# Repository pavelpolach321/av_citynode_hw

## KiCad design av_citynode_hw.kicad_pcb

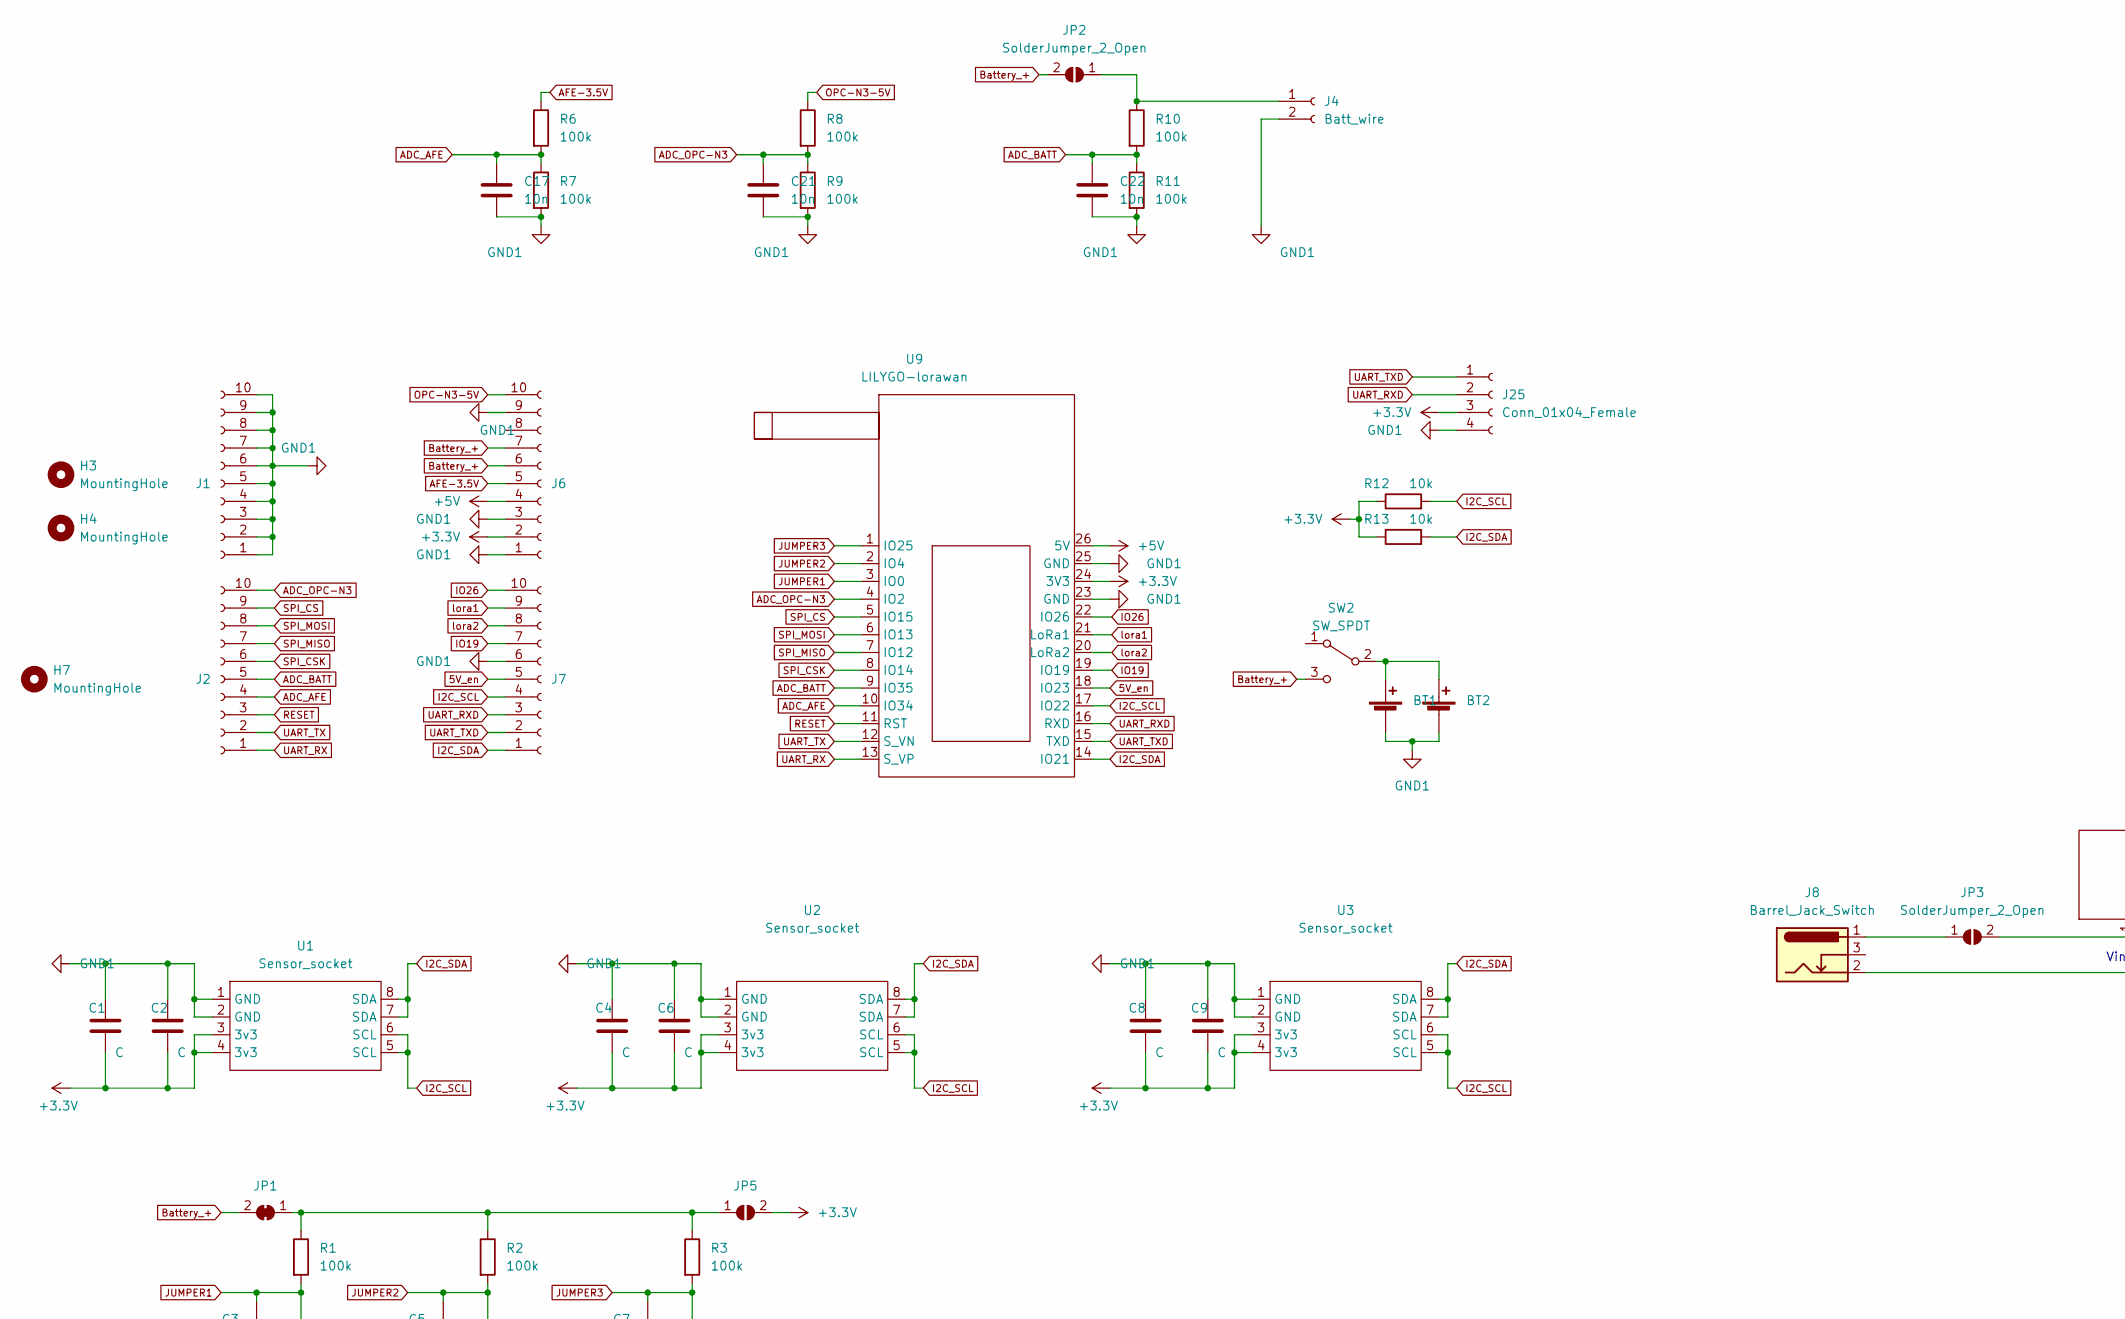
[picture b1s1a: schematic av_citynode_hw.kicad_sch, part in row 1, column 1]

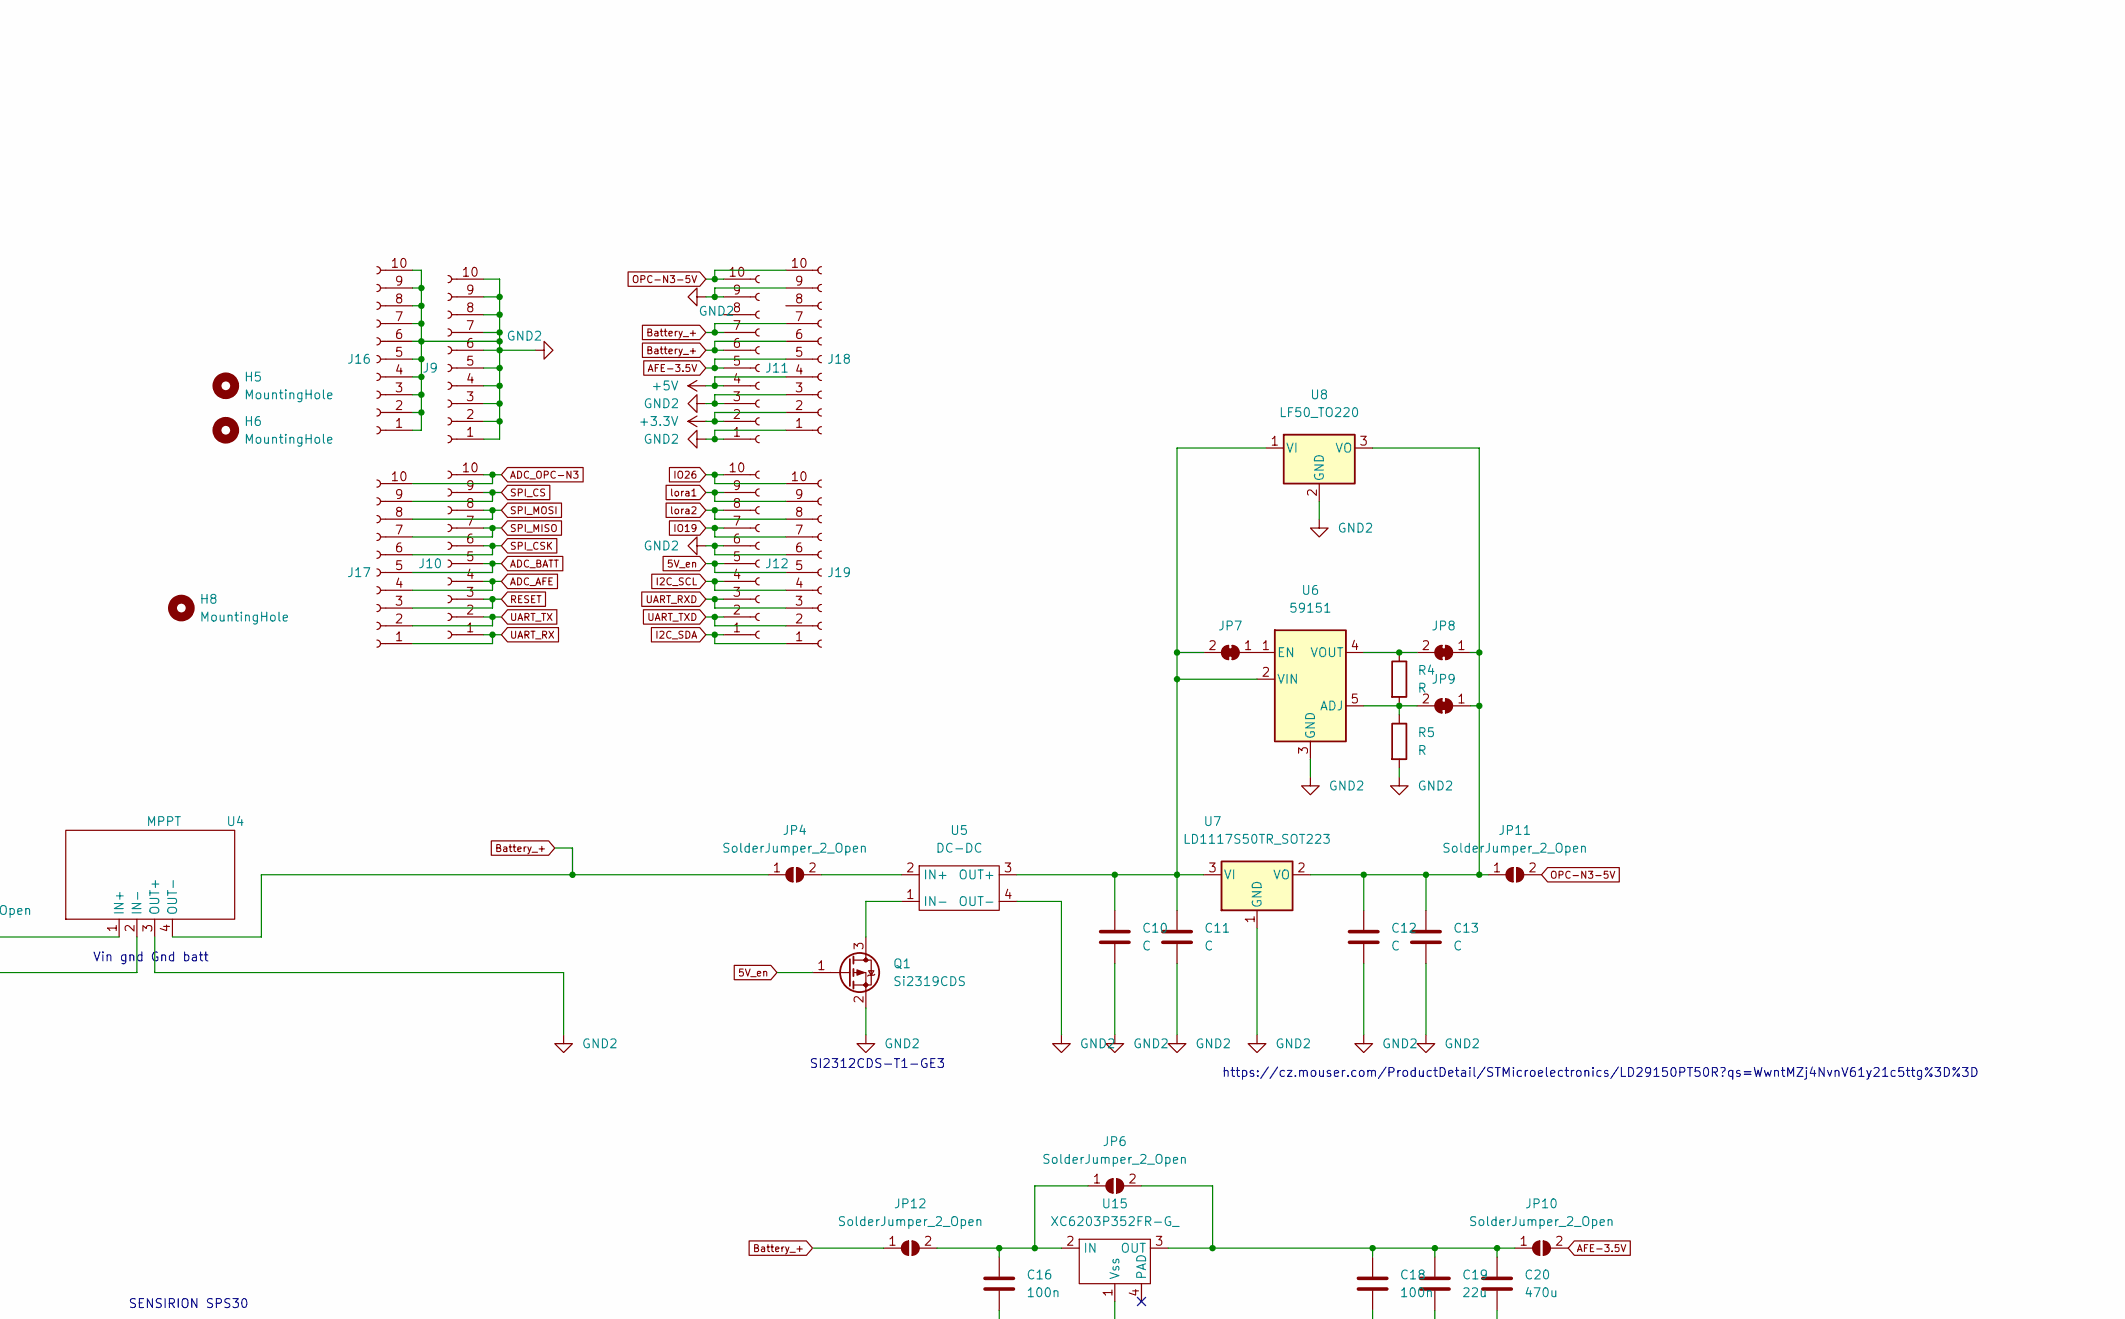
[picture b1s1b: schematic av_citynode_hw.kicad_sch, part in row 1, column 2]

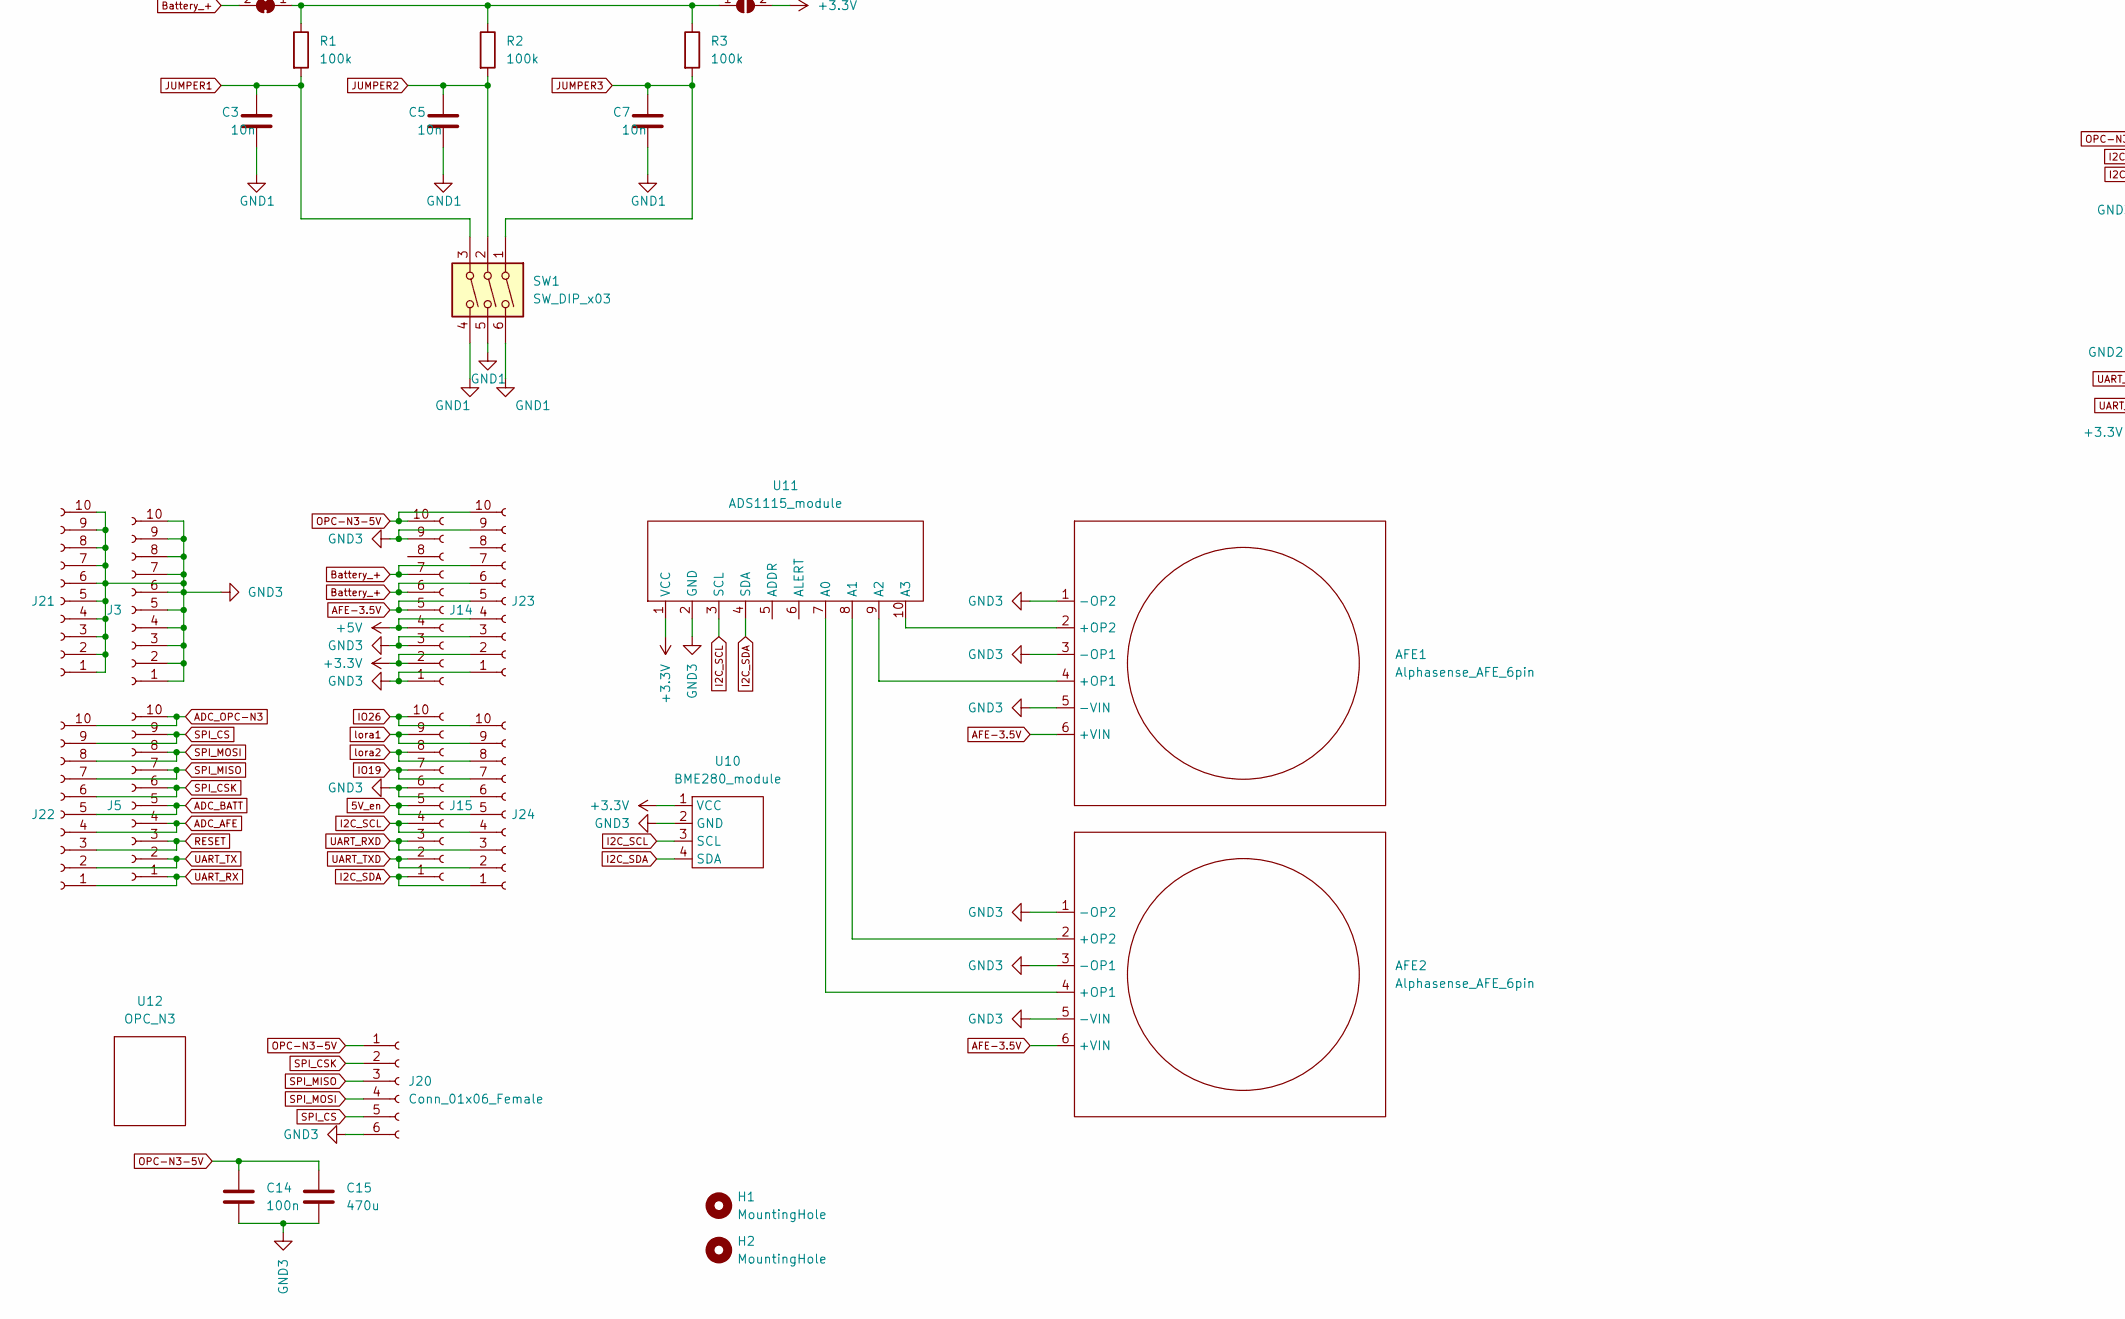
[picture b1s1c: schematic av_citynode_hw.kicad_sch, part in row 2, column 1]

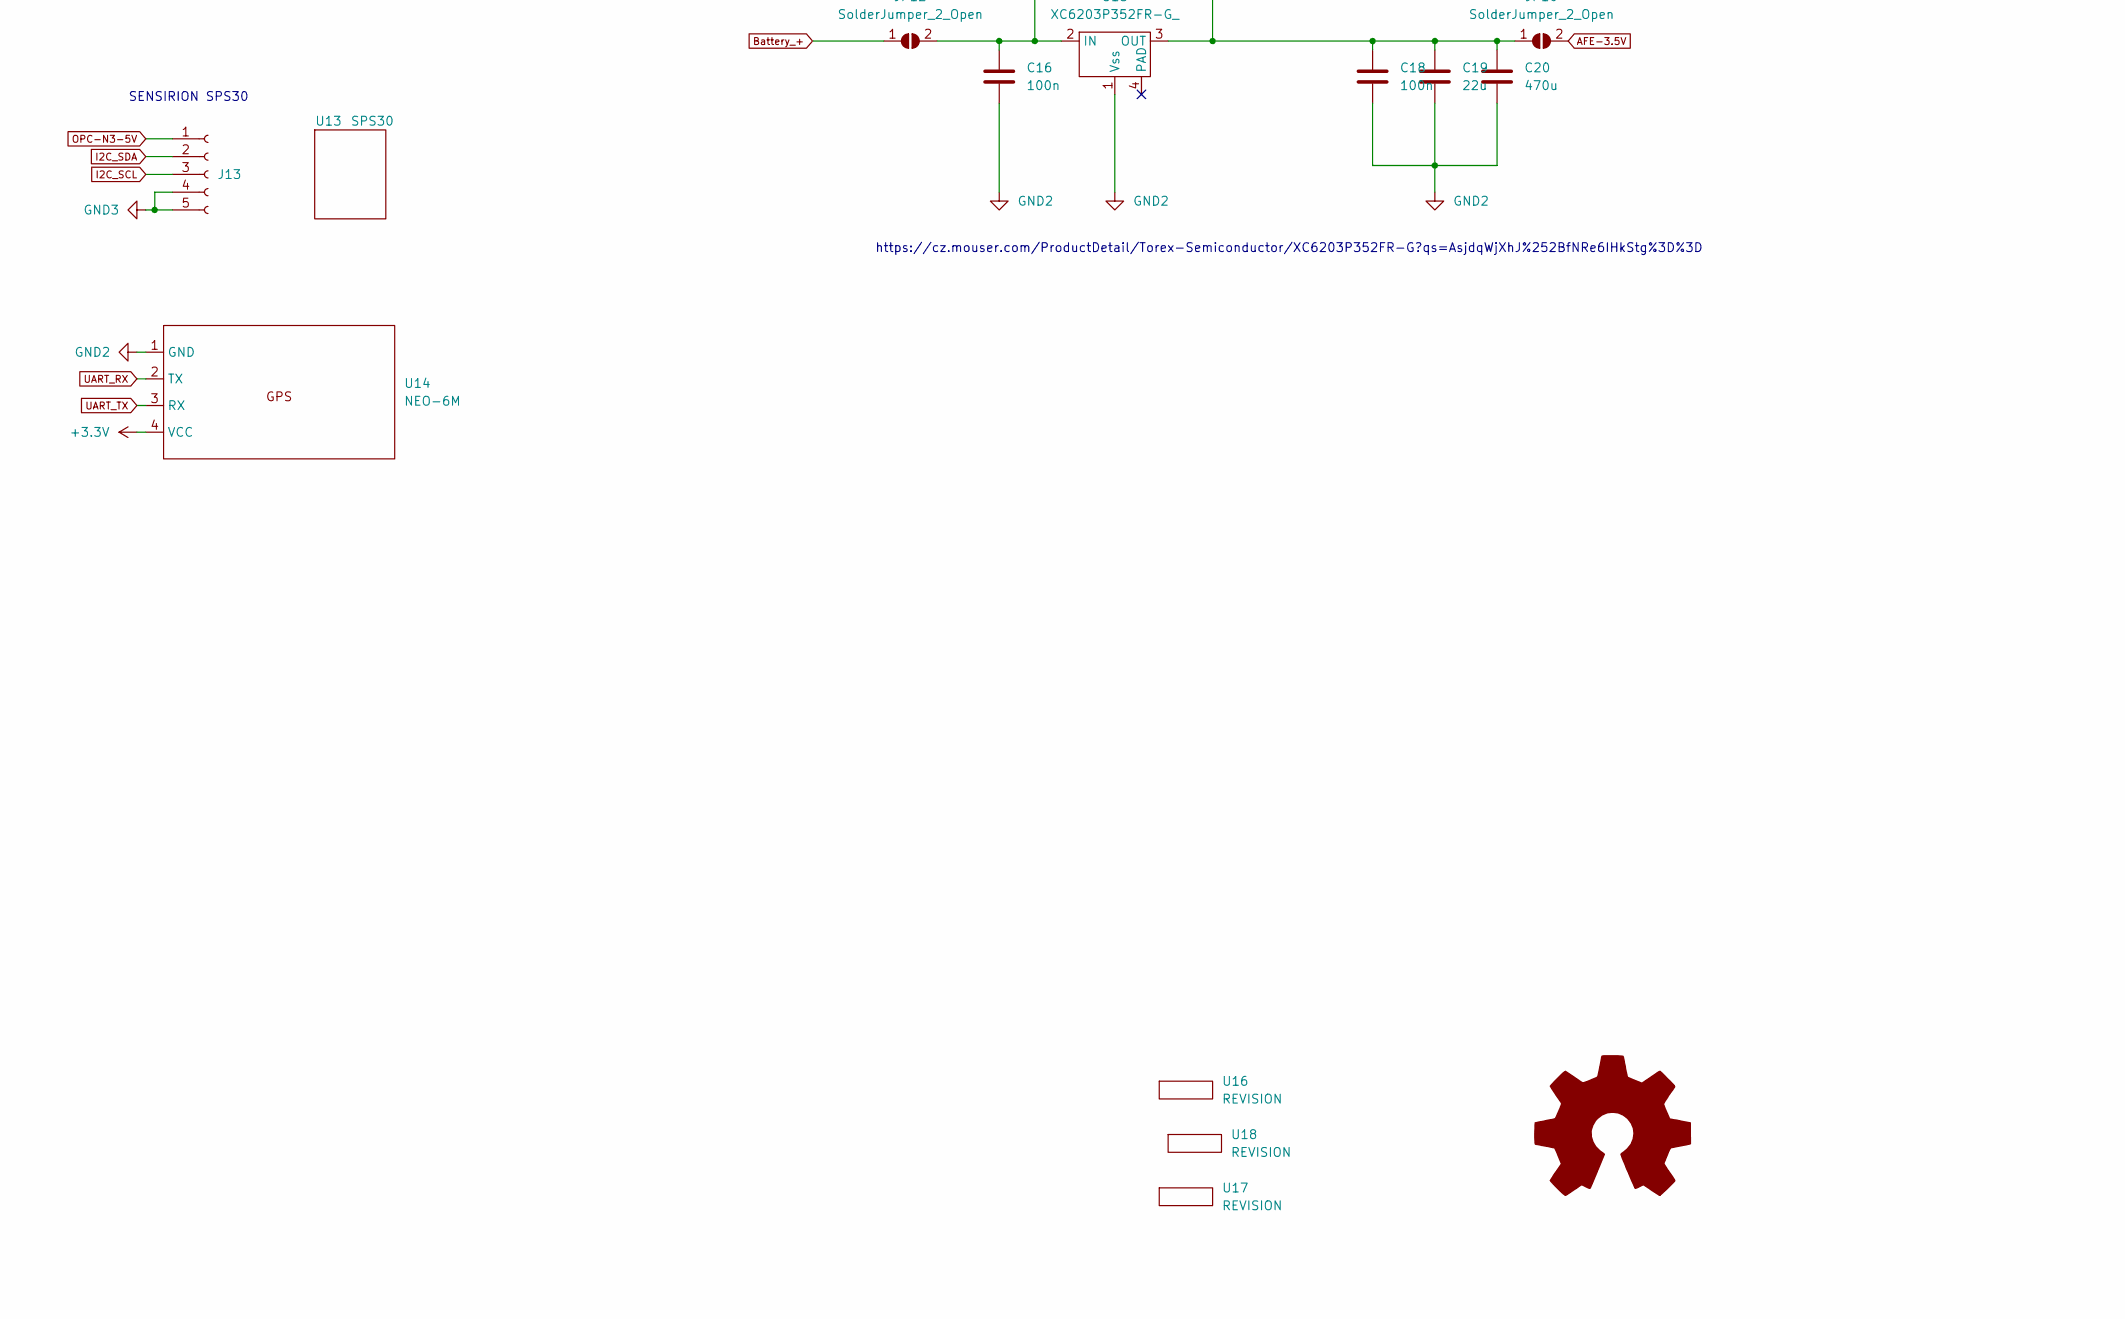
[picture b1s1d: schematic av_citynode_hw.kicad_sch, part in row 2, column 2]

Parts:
AFE1: Alphasense_AFE_6pin; Alphasense_AFE_6pin-LEFT
AFE2: Alphasense_AFE_6pin; Alphasense_AFE_6pin-RIGHT
BT1, BT2: Battery_Cell; BatteryHolder_MPD_BH-18650-PC2
C1, C2, C4, C6, C8, C9: C; C_0805_2012Metric_Pad1.18x1.45mm_HandSolder
C3, C5, C7: 10n; C_0805_2012Metric_Pad1.18x1.45mm_HandSolder
C10, C11, C12, C13: C; C_0805_2012Metric
C14, C16, C18: 100n; C_0805_2012Metric
C15: 470u; CP_Radial_D10.0mm_P3.50mm
C17, C21, C22: 10n; C_0805_2012Metric
C19: 22u; C_0805_2012Metric
C20: 470u; CP_Radial_D5.0mm_P2.50mm
H1, H2, H3, H4, H5, H6: MountingHole; MountingHole_4.3mm_M4
H7, H8: MountingHole; opc-n3-hole
J1, J2, J3, J5, J6, J7, J9, J10, J11, J12, J14, J15, J16, J17, J18, J19, J21, J22, J23, J24: Conn_01x10_Female; PinSocket_1x10_P2.54mm_Vertical
J4: Batt_wire; PinSocket_1x02_P2.54mm_Vertical
J8: Barrel_Jack_Switch; BarrelJack_Horizontal
J13: Conn_01x05_Female; PinHeader_1x05_P2.54mm_Vertical
J20: Conn_01x06_Female; PinHeader_1x06_P2.54mm_Vertical
J25: Conn_01x04_Female; PinSocket_1x04_P2.54mm_Vertical
JP1: SolderJumper_2_Bridged; SolderJumper-2_P1.3mm_Bridged_Pad1.0x1.5mm
JP2, JP3, JP4, JP6, JP10, JP11, JP12: SolderJumper_2_Open; SolderJumper-2_P1.3mm_Open_RoundedPad1.0x1.5mm
JP5: SolderJumper_2_Open; SolderJumper-2_P1.3mm_Open_Pad1.0x1.5mm
JP7, JP8, JP9: SolderJumper_2_Bridged; SolderJumper-2_P1.3mm_Open_TrianglePad1.0x1.5mm
Q1: Si2319CDS; SOT-23
R1, R2, R3: 100k; R_0805_2012Metric_Pad1.20x1.40mm_HandSolder
R4, R5: R; R_0805_2012Metric
R6, R7, R8, R9, R10, R11: 100k; R_0805_2012Metric
R12, R13: 10k; R_0805_2012Metric
SW1: SW_DIP_x03; DIP-6_W7.62mm
SW2: SW_SPDT; SW_Slide_1P2T_CK_OS102011MS2Q
U1, U2, U3: Sensor_socket; Sensor_module
U4: MPPT; DC-DC
U5: DC-DC; STEP_UP
U6: 59151; TO-263-5_TabPin3
U7: LD1117S50TR_SOT223; SOT-223-3_TabPin2
U8: LF50_TO220; TO-220-3_Vertical
U9: LILYGO-lorawan; LILYGO-LORAWAN
U10: BME280_module; BME280-module
U11: ADS1115_module; ADS1115-module
U12: OPC_N3; opc-n3
U13: SPS30
U14: NEO-6M; NEO-6M-mod
U15: XC6203P352FR-G_; SOT-223
U16, U17, U18: REVISION

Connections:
5V_en: J7.5, J12.5, J15.5, J19.5, J24.5, Q1.1 (G), U9.18 (IO23)
+3V3: C1.2, C2.2, C4.2, C6.2, C8.2, C9.2, J6.2, J11.2, J14.2, J18.2, J23.2, J25.3, JP5.2 (B), R12.1, R13.1, U1.3 (3v3), U1.4 (3v3), U2.3 (3v3), U2.4 (3v3), U3.3 (3v3), U3.4 (3v3), U9.24 (3V3), U10.1 (VCC), U11.1 (VCC), U14.4 (VCC)
+5V: J6.4, J11.4, J14.4, J18.4, J23.4, U9.26 (5V)
ADC_AFE: C17.1, J2.4, J5.4, J10.4, J17.4, J22.4, R6.2, R7.1, U9.10 (IO34)
ADC_BATT: C22.1, J2.5, J5.5, J10.5, J17.5, J22.5, R10.2, R11.1, U9.9 (IO35)
ADC_OPC-N3: C21.1, J2.10, J5.10, J10.10, J17.10, J22.10, R8.2, R9.1, U9.4 (IO2)
AFE-3.5V: AFE1.6 (+VIN), AFE2.6 (+VIN), J6.5, J11.5, J14.5, J18.5, J23.5, JP10.2 (B), R6.1
Battery_+: J6.6, J6.7, J11.6, J11.7, J14.6, J14.7, J18.6, J18.7, J23.6, J23.7, JP1.2 (B), JP2.2 (B), JP4.1 (A), JP12.1 (A), SW2.3 (C), U4.4 (OUT-)
GND1: BT1.2 (-), BT2.2 (-), C1.1, C2.1, C3.2, C4.1, C5.2, C6.1, C7.2, C8.1, C9.1, C17.2, C21.2, C22.2, J1.1, J1.2, J1.3, J1.4, J1.5, J1.6, J1.7, J1.8, J1.9, J1.10, J4.2, J6.1, J6.3, J6.9, J7.6, J25.4, R7.2, R9.2, R11.2, SW1.4, SW1.5, SW1.6, U1.1 (GND), U1.2 (GND), U2.1 (GND), U2.2 (GND), U3.1 (GND), U3.2 (GND), U9.23 (GND), U9.25 (GND)
GND2: C10.2, C11.2, C12.2, C13.2, C16.2, C18.2, C19.2, C20.2, J9.1, J9.2, J9.3, J9.4, J9.5, J9.6, J9.7, J9.8, J9.9, J9.10, J11.1, J11.3, J11.9, J12.6, J16.1, J16.2, J16.3, J16.4, J16.5, J16.6, J16.7, J16.8, J16.9, J16.10, J18.1, J18.3, J18.9, J19.6, Q1.2 (S), R5.2, U4.3 (OUT+), U5.4 (OUT-), U6.3 (GND), U7.1 (GND), U8.2 (GND), U14.1 (GND), U15.1 (Vss)
GND3: AFE1.1 (-OP2), AFE1.3 (-OP1), AFE1.5 (-VIN), AFE2.1 (-OP2), AFE2.3 (-OP1), AFE2.5 (-VIN), C14.2, C15.2, J3.1, J3.2, J3.3, J3.4, J3.5, J3.6, J3.7, J3.8, J3.9, J3.10, J13.4, J13.5, J14.1, J14.3, J14.9, J15.6, J20.6, J21.1, J21.2, J21.3, J21.4, J21.5, J21.6, J21.7, J21.8, J21.9, J21.10, J23.1, J23.3, J23.9, J24.6, U10.2 (GND), U11.2 (GND)
I2C_SCL: J7.4, J12.4, J13.3, J15.4, J19.4, J24.4, R12.2, U1.5 (SCL), U1.6 (SCL), U2.5 (SCL), U2.6 (SCL), U3.5 (SCL), U3.6 (SCL), U9.17 (IO22), U10.3 (SCL), U11.3 (SCL)
I2C_SDA: J7.1, J12.1, J13.2, J15.1, J19.1, J24.1, R13.2, U1.7 (SDA), U1.8 (SDA), U2.7 (SDA), U2.8 (SDA), U3.7 (SDA), U3.8 (SDA), U9.14 (IO21), U10.4 (SDA), U11.4 (SDA)
IO19: J7.7, J12.7, J15.7, J19.7, J24.7, U9.19 (IO19)
IO26: J7.10, J12.10, J15.10, J19.10, J24.10, U9.22 (IO26)
JUMPER1: C3.1, R1.2, SW1.3, U9.3 (IO0)
JUMPER2: C5.1, R2.2, SW1.2, U9.2 (IO4)
JUMPER3: C7.1, R3.2, SW1.1, U9.1 (IO25)
unnamed: AFE1.2 (+OP2), U11.10 (A3)
unnamed: AFE1.4 (+OP1), U11.9 (A2)
unnamed: AFE2.2 (+OP2), U11.8 (A1)
unnamed: AFE2.4 (+OP1), U11.7 (A0)
unnamed: BT1.1 (+), BT2.1 (+), SW2.2 (B)
unnamed: C10.1, C11.1, JP7.2 (B), U5.3 (OUT+), U6.2 (VIN), U7.3 (VI), U8.1 (VI)
unnamed: C12.1, C13.1, JP8.1 (A), JP9.1 (A), JP11.1 (A), U7.2 (VO), U8.3 (VO)
unnamed: C16.1, JP6.1 (A), JP12.2 (B), U15.2 (IN)
unnamed: C18.1, C19.1, C20.1, JP6.2 (B), JP10.1 (A), U15.3 (OUT)
unnamed: J8.1, JP3.1 (A)
unnamed: J8.2, U4.2 (IN-)
unnamed: JP1.1 (A), JP5.1 (A), R1.1, R2.1, R3.1
unnamed: JP7.1 (A), U6.1 (EN)
unnamed: JP8.2 (B), R4.1, U6.4 (VOUT)
unnamed: JP9.2 (B), R4.2, R5.1, U6.5 (ADJ)
unnamed: Q1.3 (D), U5.1 (IN-)
unnamed: J4.1, JP2.1 (A), R10.1
unnamed: JP3.2 (B), U4.1 (IN+)
unnamed: JP4.2 (B), U5.2 (IN+)
OPC-N3-5V: C14.1, C15.1, J6.10, J11.10, J13.1, J14.10, J18.10, J20.1, J23.10, JP11.2 (B), R8.1
RESET: J2.3, J5.3, J10.3, J17.3, J22.3, U9.11 (RST)
SPI_CS: J2.9, J5.9, J10.9, J17.9, J20.5, J22.9, U9.5 (IO15)
SPI_CSK: J2.6, J5.6, J10.6, J17.6, J20.2, J22.6, U9.8 (IO14)
SPI_MISO: J2.7, J5.7, J10.7, J17.7, J20.3, J22.7, U9.7 (IO12)
SPI_MOSI: J2.8, J5.8, J10.8, J17.8, J20.4, J22.8, U9.6 (IO13)
UART_RX: J2.1, J5.1, J10.1, J17.1, J22.1, U9.13 (S_VP), U14.2 (TX)
UART_RXD: J7.3, J12.3, J15.3, J19.3, J24.3, J25.2, U9.16 (RXD)
UART_TX: J2.2, J5.2, J10.2, J17.2, J22.2, U9.12 (S_VN), U14.3 (RX)
UART_TXD: J7.2, J12.2, J15.2, J19.2, J24.2, J25.1, U9.15 (TXD)
lora1: J7.9, J12.9, J15.9, J19.9, J24.9, U9.21 (LoRa1)
lora2: J7.8, J12.8, J15.8, J19.8, J24.8, U9.20 (LoRa2)

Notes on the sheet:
Vin gnd Gnd batt
SI2312CDS-T1-GE3
https://cz.mouser.com/ProductDetail/STMicroelectronics/LD29150PT50R?qs=WwntMZj4NvnV61y21c5ttg%3D%3D
SENSIRION SPS30
https://cz.mouser.com/ProductDetail/Torex-Semiconductor/XC6203P352FR-G?qs=AsjdqWjXhJ%252BfNRe6IHkStg%3D%3D

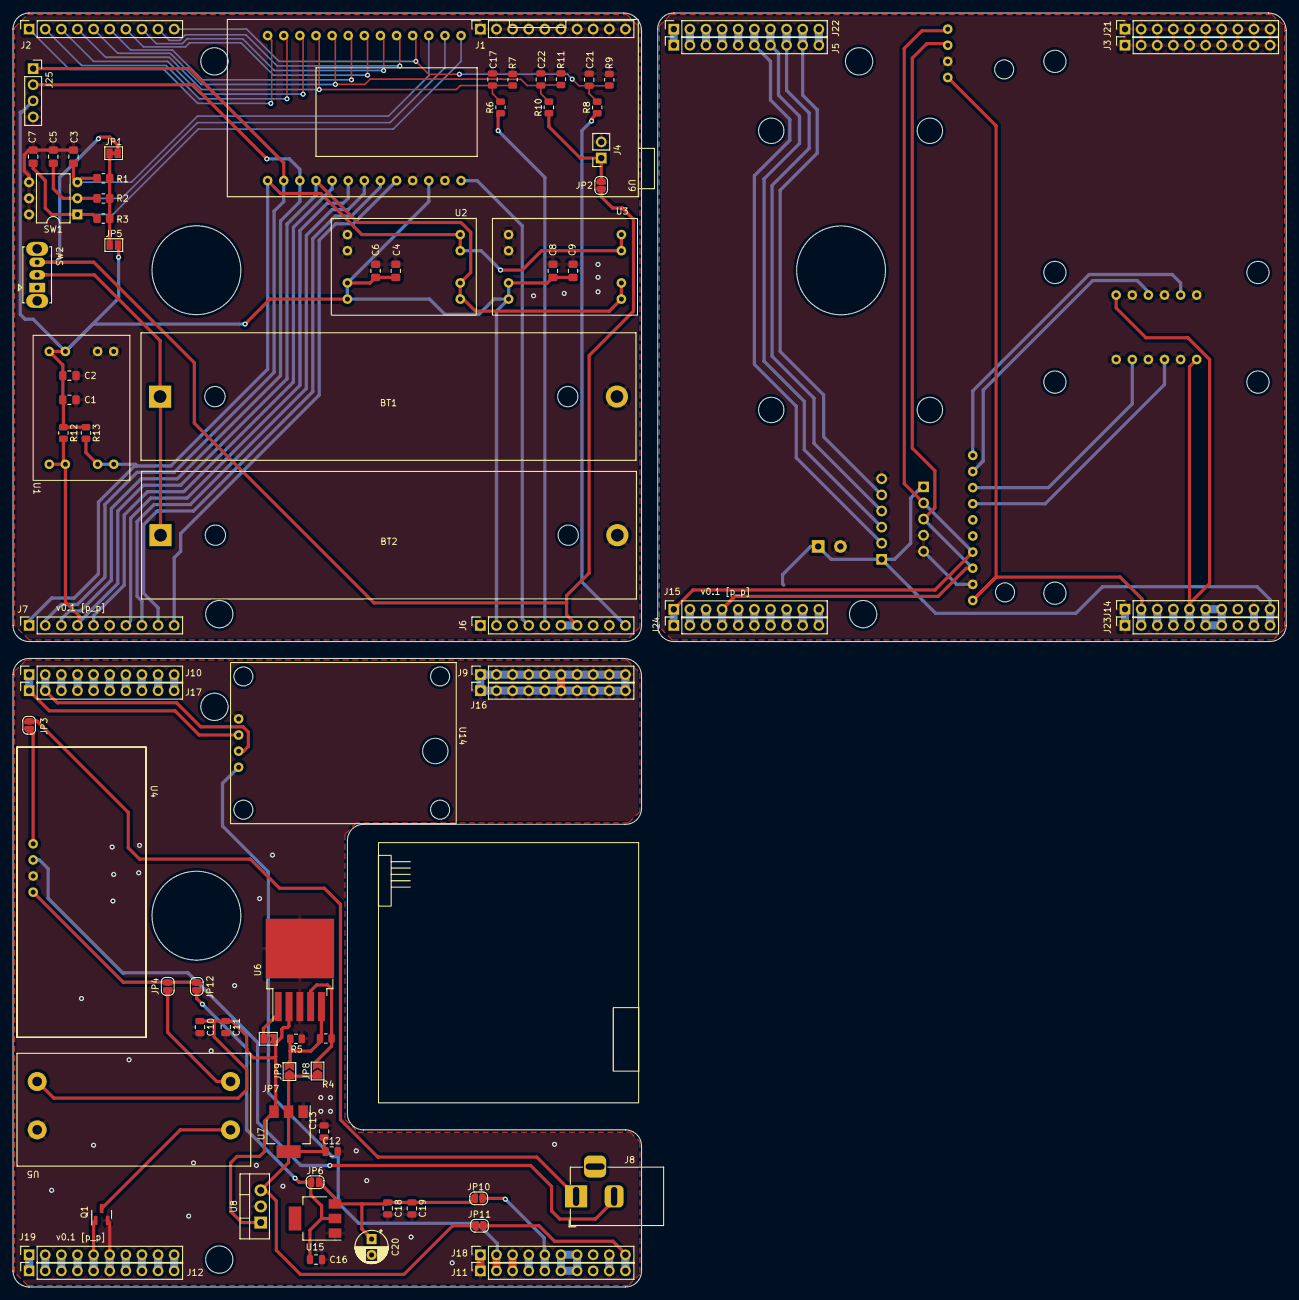
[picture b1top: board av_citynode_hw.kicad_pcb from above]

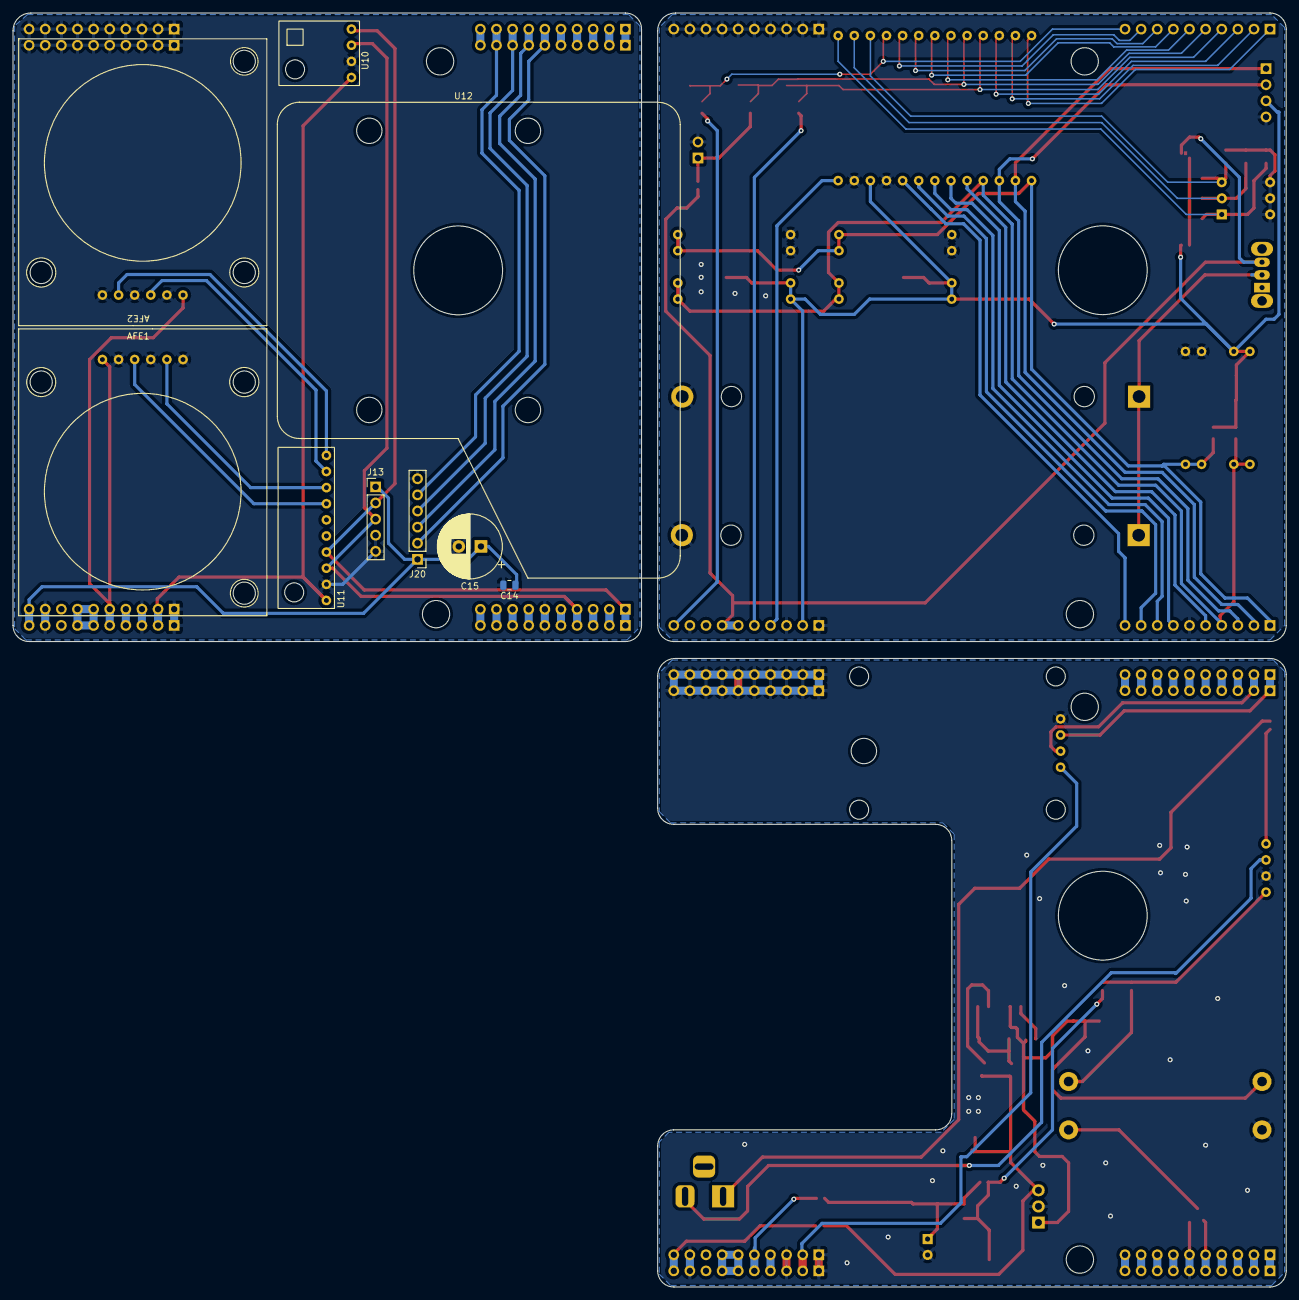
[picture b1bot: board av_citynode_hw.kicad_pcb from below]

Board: 2 copper layers, 200.7 x 200.8 mm, 105 parts (9 on the bottom side), 49 nets.

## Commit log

2022-10-26 initial
